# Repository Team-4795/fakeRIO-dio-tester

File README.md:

# fakeRIO-dio-tester
Power source and signal tester for digital I/O devices as used in FRC

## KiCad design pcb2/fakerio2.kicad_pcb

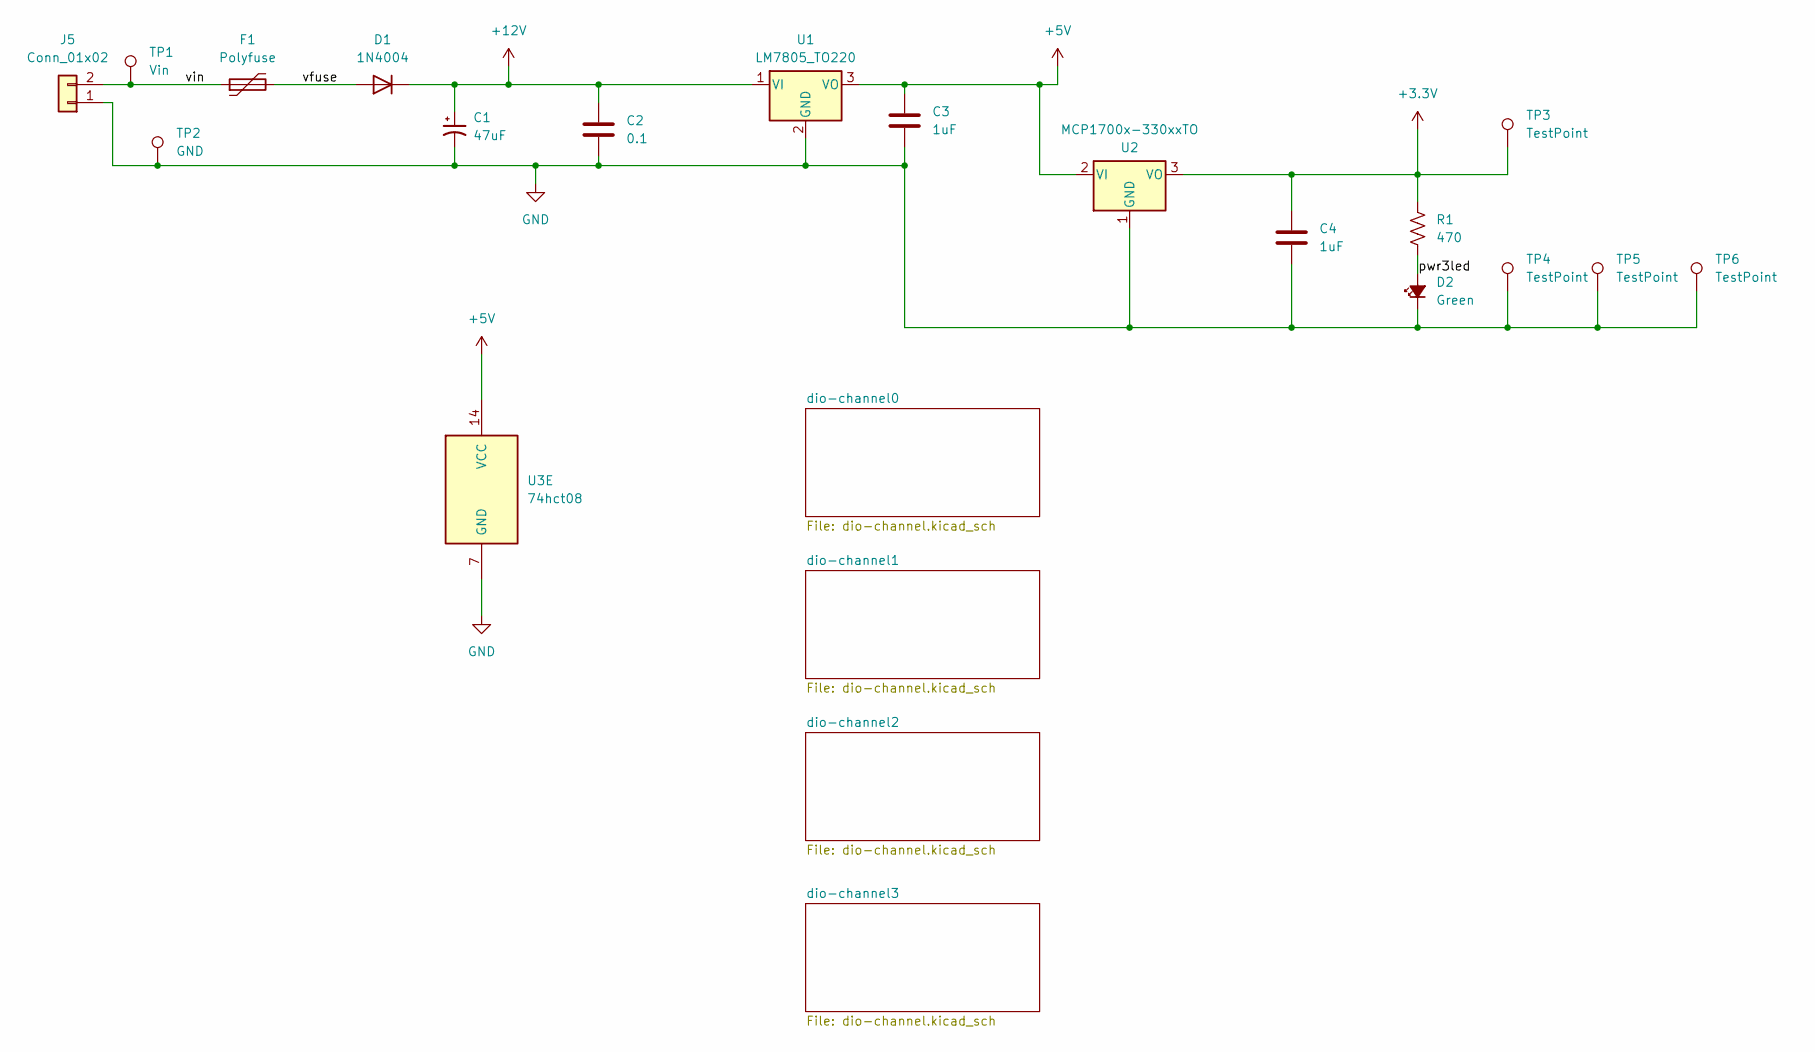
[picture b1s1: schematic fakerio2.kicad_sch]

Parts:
C1: 47uF; CP_Radial_D6.3mm_P2.50mm
C2: 0.1; C_Rect_L4.0mm_W2.5mm_P2.50mm
C3, C4: 1uF; C_Rect_L7.0mm_W4.5mm_P5.00mm
D1: 1N4004; D_DO-41_SOD81_P10.16mm_Horizontal
D2: Green; LED_D5.0mm
F1: Polyfuse; C_Disc_D11.0mm_W5.0mm_P5.00mm
J5: Conn_01x02; PinHeader_1x02_P2.54mm_Vertical
R1: 470; R_Axial_DIN0207_L6.3mm_D2.5mm_P10.16mm_Horizontal
TP1: Vin; MountingHole_3mm_Pad_Via
TP2: GND; MountingHole_3mm_Pad_Via
TP3, TP4, TP5, TP6: TestPoint; PinHeader_1x01_P2.54mm_Vertical
U1: LM7805_TO220; TO-220-3_Horizontal_TabDown
U2: MCP1700x-330xxTO; TO-92_Inline
U3: 74hct08; DIP-14_W7.62mm_Socket

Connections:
+3.3V: C4.1, R1.1, TP3.1, U2.3 (VO); also elsewhere on the board
+5V: C3.1, U1.3 (VO), U2.2 (VI), U3.4, U3.9, U3.12, U3.14 (VCC); also elsewhere on the board
+12V: C1.1, C2.1, D1.1 (K), U1.1 (VI)
/dio-channel1/ibuf_out: U3.6; also elsewhere on the board
/dio-channel1/iopin_prot: U3.5; also elsewhere on the board
/dio-channel2/ibuf_out: U3.8; also elsewhere on the board
/dio-channel2/iopin_prot: U3.10; also elsewhere on the board
/dio-channel3/ibuf_out: U3.11; also elsewhere on the board
/dio-channel3/iopin_prot: U3.13; also elsewhere on the board
/pwr3led: D2.2 (A), R1.2
/vfuse: D1.2 (A), F1.2
/vin: F1.1, J5.2, TP1.1
GND: C1.2, C2.2, C3.2, C4.2, D2.1 (K), J5.1, TP2.1, TP4.1, TP5.1, TP6.1, U1.2 (GND), U2.1 (GND), U3.7 (GND); also elsewhere on the board

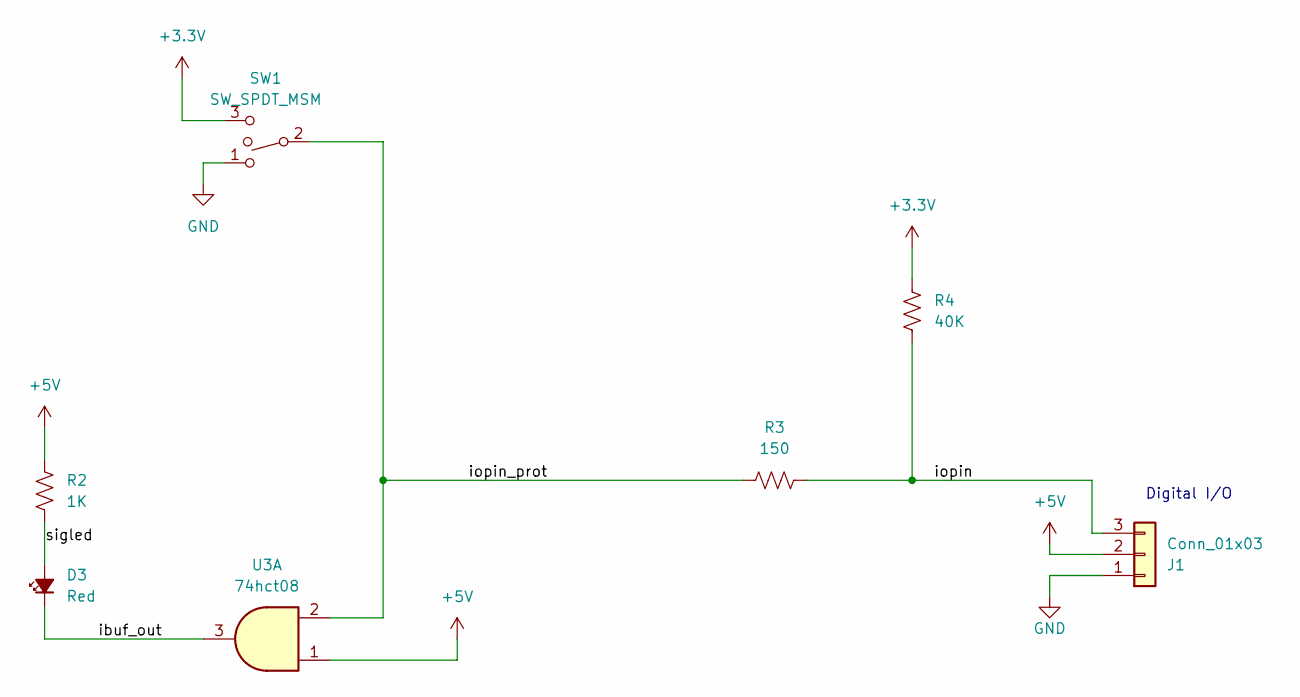
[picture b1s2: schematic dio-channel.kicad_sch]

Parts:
D3: Red; LED_D5.0mm
J1: Conn_01x03; PinHeader_1x03_P2.54mm_Vertical
R2: 1K; R_Axial_DIN0207_L6.3mm_D2.5mm_P10.16mm_Horizontal
R3: 150; R_Axial_DIN0207_L6.3mm_D2.5mm_P10.16mm_Horizontal
R4: 40K; R_Axial_DIN0207_L6.3mm_D2.5mm_P10.16mm_Horizontal
SW1: SW_SPDT_MSM; SPDT-ESwitch-100SP3-M2
U3: 74hct08; DIP-14_W7.62mm_Socket

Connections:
+3.3V: R4.1, SW1.3; also elsewhere on the board
+5V: J1.2, R2.1, U3.1, U3.4, U3.9, U3.12; also elsewhere on the board
/dio-channel0/ibuf_out: D3.1 (K), U3.3
/dio-channel0/iopin: J1.3, R3.2, R4.2
/dio-channel0/iopin_prot: R3.1, SW1.2, U3.2
/dio-channel0/sigled: D3.2 (A), R2.2
/dio-channel1/ibuf_out: U3.6; also elsewhere on the board
/dio-channel1/iopin_prot: U3.5; also elsewhere on the board
/dio-channel2/ibuf_out: U3.8; also elsewhere on the board
/dio-channel2/iopin_prot: U3.10; also elsewhere on the board
/dio-channel3/ibuf_out: U3.11; also elsewhere on the board
/dio-channel3/iopin_prot: U3.13; also elsewhere on the board
GND: J1.1, SW1.1; also elsewhere on the board

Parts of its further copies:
D4, D5, D6: Red; LED_D5.0mm
J2, J3, J4: Conn_01x03; PinHeader_1x03_P2.54mm_Vertical
R5, R8, R11: 1K; R_Axial_DIN0207_L6.3mm_D2.5mm_P10.16mm_Horizontal
R6, R9, R12: 150; R_Axial_DIN0207_L6.3mm_D2.5mm_P10.16mm_Horizontal
R7, R10, R13: 40K; R_Axial_DIN0207_L6.3mm_D2.5mm_P10.16mm_Horizontal
SW2, SW3, SW4: SW_SPDT_MSM; SPDT-ESwitch-100SP3-M2

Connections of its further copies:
+3.3V: R7.1, R10.1, R13.1, SW2.3, SW3.3, SW4.3; also elsewhere on the board
+5V: J2.2, J3.2, J4.2, R5.1, R8.1, R11.1; also elsewhere on the board
/dio-channel1/ibuf_out: D4.1 (K); also elsewhere on the board
/dio-channel1/iopin: J2.3, R6.2, R7.2
/dio-channel1/iopin_prot: R6.1, SW2.2; also elsewhere on the board
/dio-channel1/sigled: D4.2 (A), R5.2
/dio-channel2/ibuf_out: D5.1 (K); also elsewhere on the board
/dio-channel2/iopin: J3.3, R9.2, R10.2
/dio-channel2/iopin_prot: R9.1, SW3.2; also elsewhere on the board
/dio-channel2/sigled: D5.2 (A), R8.2
/dio-channel3/ibuf_out: D6.1 (K); also elsewhere on the board
/dio-channel3/iopin: J4.3, R12.2, R13.2
/dio-channel3/iopin_prot: R12.1, SW4.2; also elsewhere on the board
/dio-channel3/sigled: D6.2 (A), R11.2
GND: J2.1, J3.1, J4.1, SW2.1, SW3.1, SW4.1; also elsewhere on the board

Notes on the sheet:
Digital I/O

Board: 2 copper layers, 42 parts (0 on the bottom side), 23 nets, no tracks yet.

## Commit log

2024-01-07 copy in old schematic, start new schematic old schematic from 2018 wiki page start new one from scratch, attempting to do hierarchical for the several channels
2024-01-16 create fooprint for e-switch switch for SW1 etc get to a pretty good part placement, but want to try a variation
2024-01-20 one more submit before rearranging layout part placement
